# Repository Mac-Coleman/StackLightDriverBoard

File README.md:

# Stack Light Driver Board

This repository hosts my KiCad project.

Currently there is only a schematic.

Footprints and 3D models of most components are provided by [CDFER's JLCPCB component library for KiCad](https://github.com/CDFER/JLCPCB-Kicad-Library).

## Footprints and 3D models of the following components provided by SnapMagic:
* TSR_1-2433E
* 282837-2
* B2B-XH-A
* ESP32-S3-WROOM-1-N4
* PJ-102AH

## 3D models provided by Adafruit:
* MAX98357

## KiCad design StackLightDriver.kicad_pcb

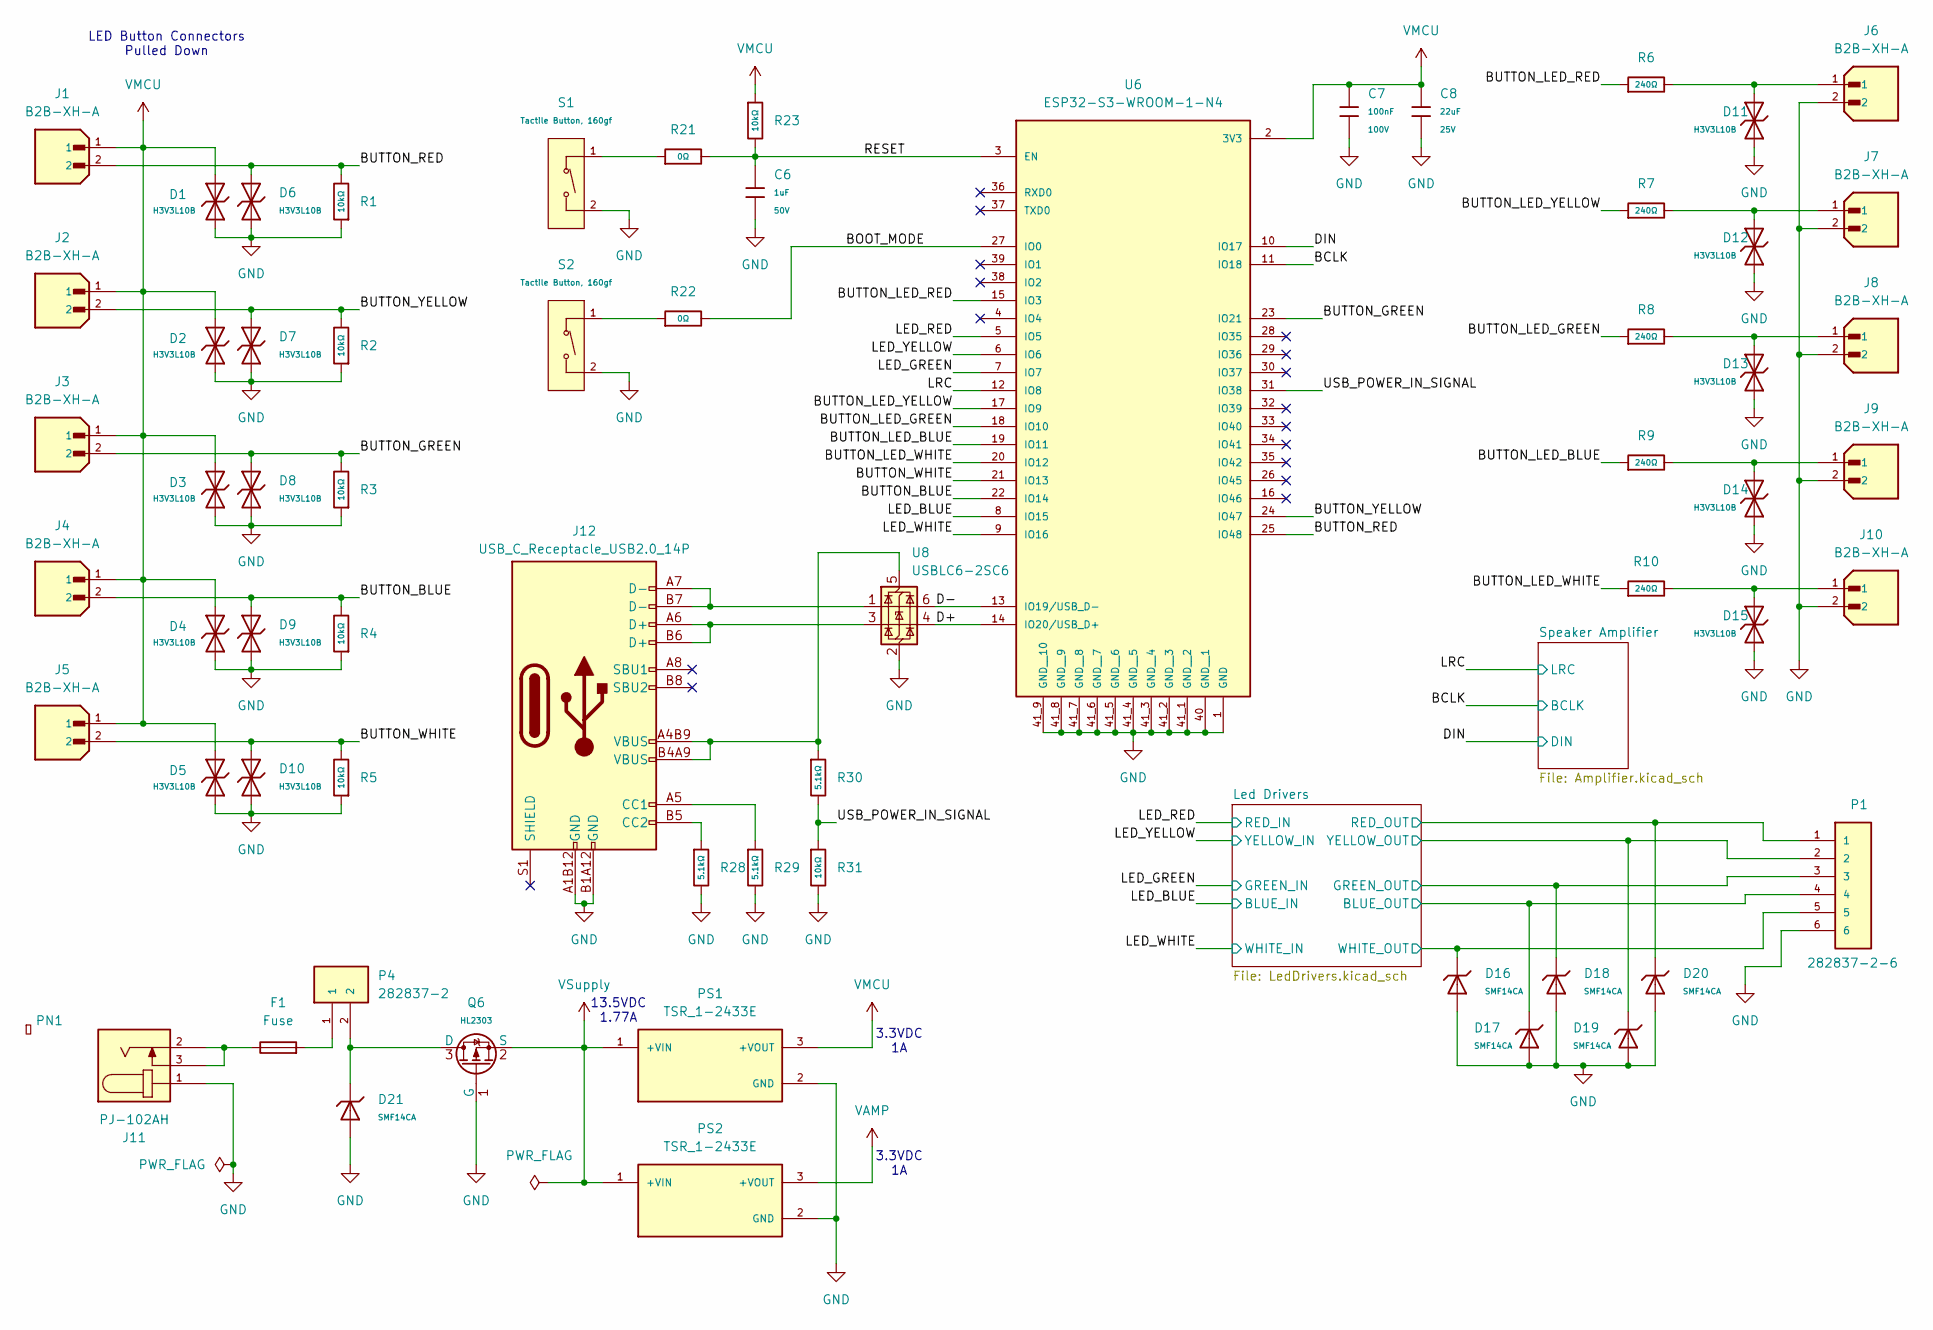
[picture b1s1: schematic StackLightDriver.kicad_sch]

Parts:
C6: 1uF; C_0805; Voltage Rated 50V; Tolerance ±10%; Part CL21B105KBFNNNE; LCSC C28323
C7: 100nF; C_0805; Voltage Rated 100V; Tolerance ±10%; Part CL21B104KCFNNNE; LCSC C28233
C8: 22uF; C_0805; Voltage Rated 25V; Tolerance ±20%; Part CL21A226MAQNNNE; LCSC C45783
D1, D2, D3, D4, D5, D6, D7, D8, D9, D10, D11, D12, D13, D14, D15: H3V3L10B; D_DFN1006-2L; Breakdown Voltage 5.5V; Part H3V3L10B; LCSC C20615781
D16, D17, D18, D19, D20, D21: SMF14CA; D_SOD-123FL; Part SMF14CA; LCSC C41411783
F1: Fuse; Fuseholder_Clip-5x20mm_Littelfuse_111_Lateral_P18.80x5.00mm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
J1, J2, J3, J4, J5, J6, J7, J8, J9, J10: B2B-XH-A; JST_B2B-XH-A; PARTREV N/A
J11: PJ-102AH; CUI_PJ-102AH
J12: USB_C_Receptacle_USB2.0_14P
P1: 282837-2-6; TE_282837-2-6; PARTREV G3
P4: 282837-2; TE_282837-2; PARTREV G3
PN1: Part_Num_JLCPCB
PS1, PS2: TSR_1-2433E; CONV_TSR_1-2433E; PARTREV May 25, 2020
Q6: HL2303; Q_SOT-23; Part HL2303; LCSC C7420345
R1, R2, R3, R4, R5, R23, R31: 10kΩ; R_0805; Overload Voltage (Max) 150V; Tolerance ±1%; Part 0805W8F1002T5E; LCSC C17414
R6, R7, R8, R9, R10: 240Ω; R_0805; Overload Voltage (Max) 150V; Tolerance ±1%; Part 0805W8F2400T5E; LCSC C17572
R21, R22: 0Ω; R_0805; Overload Voltage (Max) 150V; Tolerance ±1%; Part 0805W8F0000T5E; LCSC C17477
R28, R29, R30: 5.1kΩ; R_0805; Overload Voltage (Max) 150V; Tolerance ±1%; Part 0805W8F5101T5E; LCSC C27834
S1, S2: Tactile Button, 160gf; SW_TS-1088-AR02016; Voltage Rating (Dc) 12V; Part TS-1088-AR02016; LCSC C720477
U6: ESP32-S3-WROOM-1-N4; XCVR_ESP32-S3-WROOM-1-N4; PARTREV v1.0; Digikey 1965-ESP32-S3-WROOM-1-N4CT-ND
U8: USBLC6-2SC6; SOT-23-6; Digikey 497-5235-1-ND

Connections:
/BCLK: U6.11 (IO18); also elsewhere on the board
/BOOT_MODE: R22.2, U6.27 (IO0)
/BUTTON_BLUE: D9.2, J4.2, R4.2, U6.22 (IO14)
/BUTTON_GREEN: D8.2, J3.2, R3.2, U6.23 (IO21)
/BUTTON_LED_BLUE: R9.1, U6.19 (IO11)
/BUTTON_LED_GREEN: R8.1, U6.18 (IO10)
/BUTTON_LED_RED: R6.1, U6.15 (IO3)
/BUTTON_LED_WHITE: R10.1, U6.20 (IO12)
/BUTTON_LED_YELLOW: R7.1, U6.17 (IO9)
/BUTTON_RED: D6.2, J1.2, R1.2, U6.25 (IO48)
/BUTTON_WHITE: D10.2, J5.2, R5.2, U6.21 (IO13)
/BUTTON_YELLOW: D7.2, J2.2, R2.2, U6.24 (IO47)
/D+: U6.14 (IO20/USB_D+), U8.4 (I/O2)
/D-: U6.13 (IO19/USB_D-), U8.6 (I/O1)
/DIN: U6.10 (IO17); also elsewhere on the board
/LED_BLUE: U6.8 (IO15); also elsewhere on the board
/LED_GREEN: U6.7 (IO7); also elsewhere on the board
/LED_RED: U6.5 (IO5); also elsewhere on the board
/LED_WHITE: U6.9 (IO16); also elsewhere on the board
/LED_YELLOW: U6.6 (IO6); also elsewhere on the board
/LRC: U6.12 (IO8); also elsewhere on the board
/Led Drivers/BLUE_OUT: D17.1, P1.4; also elsewhere on the board
/Led Drivers/GREEN_OUT: D18.1, P1.3; also elsewhere on the board
/Led Drivers/RED_OUT: D20.1, P1.1; also elsewhere on the board
/Led Drivers/WHITE_OUT: D16.1, P1.5; also elsewhere on the board
/Led Drivers/YELLOW_OUT: D19.1, P1.2; also elsewhere on the board
/RESET: C6.1, R21.2, R23.2, U6.3 (EN)
/USB_POWER_IN_SIGNAL: R30.2, R31.1, U6.31 (IO38)
GND: C6.2, C7.2, C8.2, D1.1, D2.1, D3.1, D4.1, D5.1, D6.1, D7.1, D8.1, D9.1, D10.1, D11.1, D12.1, D13.1, D14.1, D15.1, D16.2, D17.2, D18.2, D19.2, D20.2, D21.2, J6.2, J7.2, J8.2, J9.2, J10.2, J11.1, J12.A1B12 (GND), J12.B1A12 (GND), P1.6, PS1.2 (GND), PS2.2 (GND), Q6.1 (G), R1.1, R2.1, R3.1, R4.1, R5.1, R28.2, R29.2, R31.2, S1.2 (B), S2.2 (B), U6.1 (GND), U6.40 (GND__1), U6.41_1 (GND__2), U6.41_2 (GND__3), U6.41_3 (GND__4), U6.41_4 (GND__5), U6.41_5 (GND__6), U6.41_6 (GND__7), U6.41_7 (GND__8), U6.41_8 (GND__9), U6.41_9 (GND__10), U6.41_10 (GND__11), U6.41_11 (GND__12), U6.41_12 (GND__13), U6.41_13 (GND__14), U6.41_14 (GND__15), U6.41_15 (GND__16), U6.41_16 (GND__17), U6.41_17 (GND__18), U6.41_18 (GND__19), U6.41_19 (GND__20), U6.41_20 (GND__21), U6.41_21 (GND__22), U8.2 (GND); also elsewhere on the board
unnamed: D11.2, J6.1, R6.2
unnamed: D12.2, J7.1, R7.2
unnamed: D13.2, J8.1, R8.2
unnamed: D14.2, J9.1, R9.2
unnamed: D15.2, J10.1, R10.2
unnamed: F1.1, J11.2, J11.3
unnamed: F1.2, P4.1
unnamed: J12.A5 (CC1), R29.1
unnamed: J12.B5 (CC2), R28.1
unnamed: J12.A6 (D+), J12.B6 (D+), U8.3 (I/O2)
unnamed: J12.A7 (D-), J12.B7 (D-), U8.1 (I/O1)
unnamed: D21.1, P4.2, Q6.3 (D)
unnamed: R21.1, S1.1 (A)
unnamed: R22.1, S2.1 (A)
unnamed: J12.A4B9 (VBUS), J12.B4A9 (VBUS), R30.1, U8.5 (VBUS)
VAMP: PS2.3 (+VOUT); also elsewhere on the board
VMCU: C7.1, C8.1, D1.2, D2.2, D3.2, D4.2, D5.2, J1.1, J2.1, J3.1, J4.1, J5.1, PS1.3 (+VOUT), R23.1, U6.2 (3V3)
VSupply: PS1.1 (+VIN), PS2.1 (+VIN), Q6.2 (S); also elsewhere on the board

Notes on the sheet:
3.3VDC 1A
13.5VDC 1.77A
LED Button Connectors Pulled Down

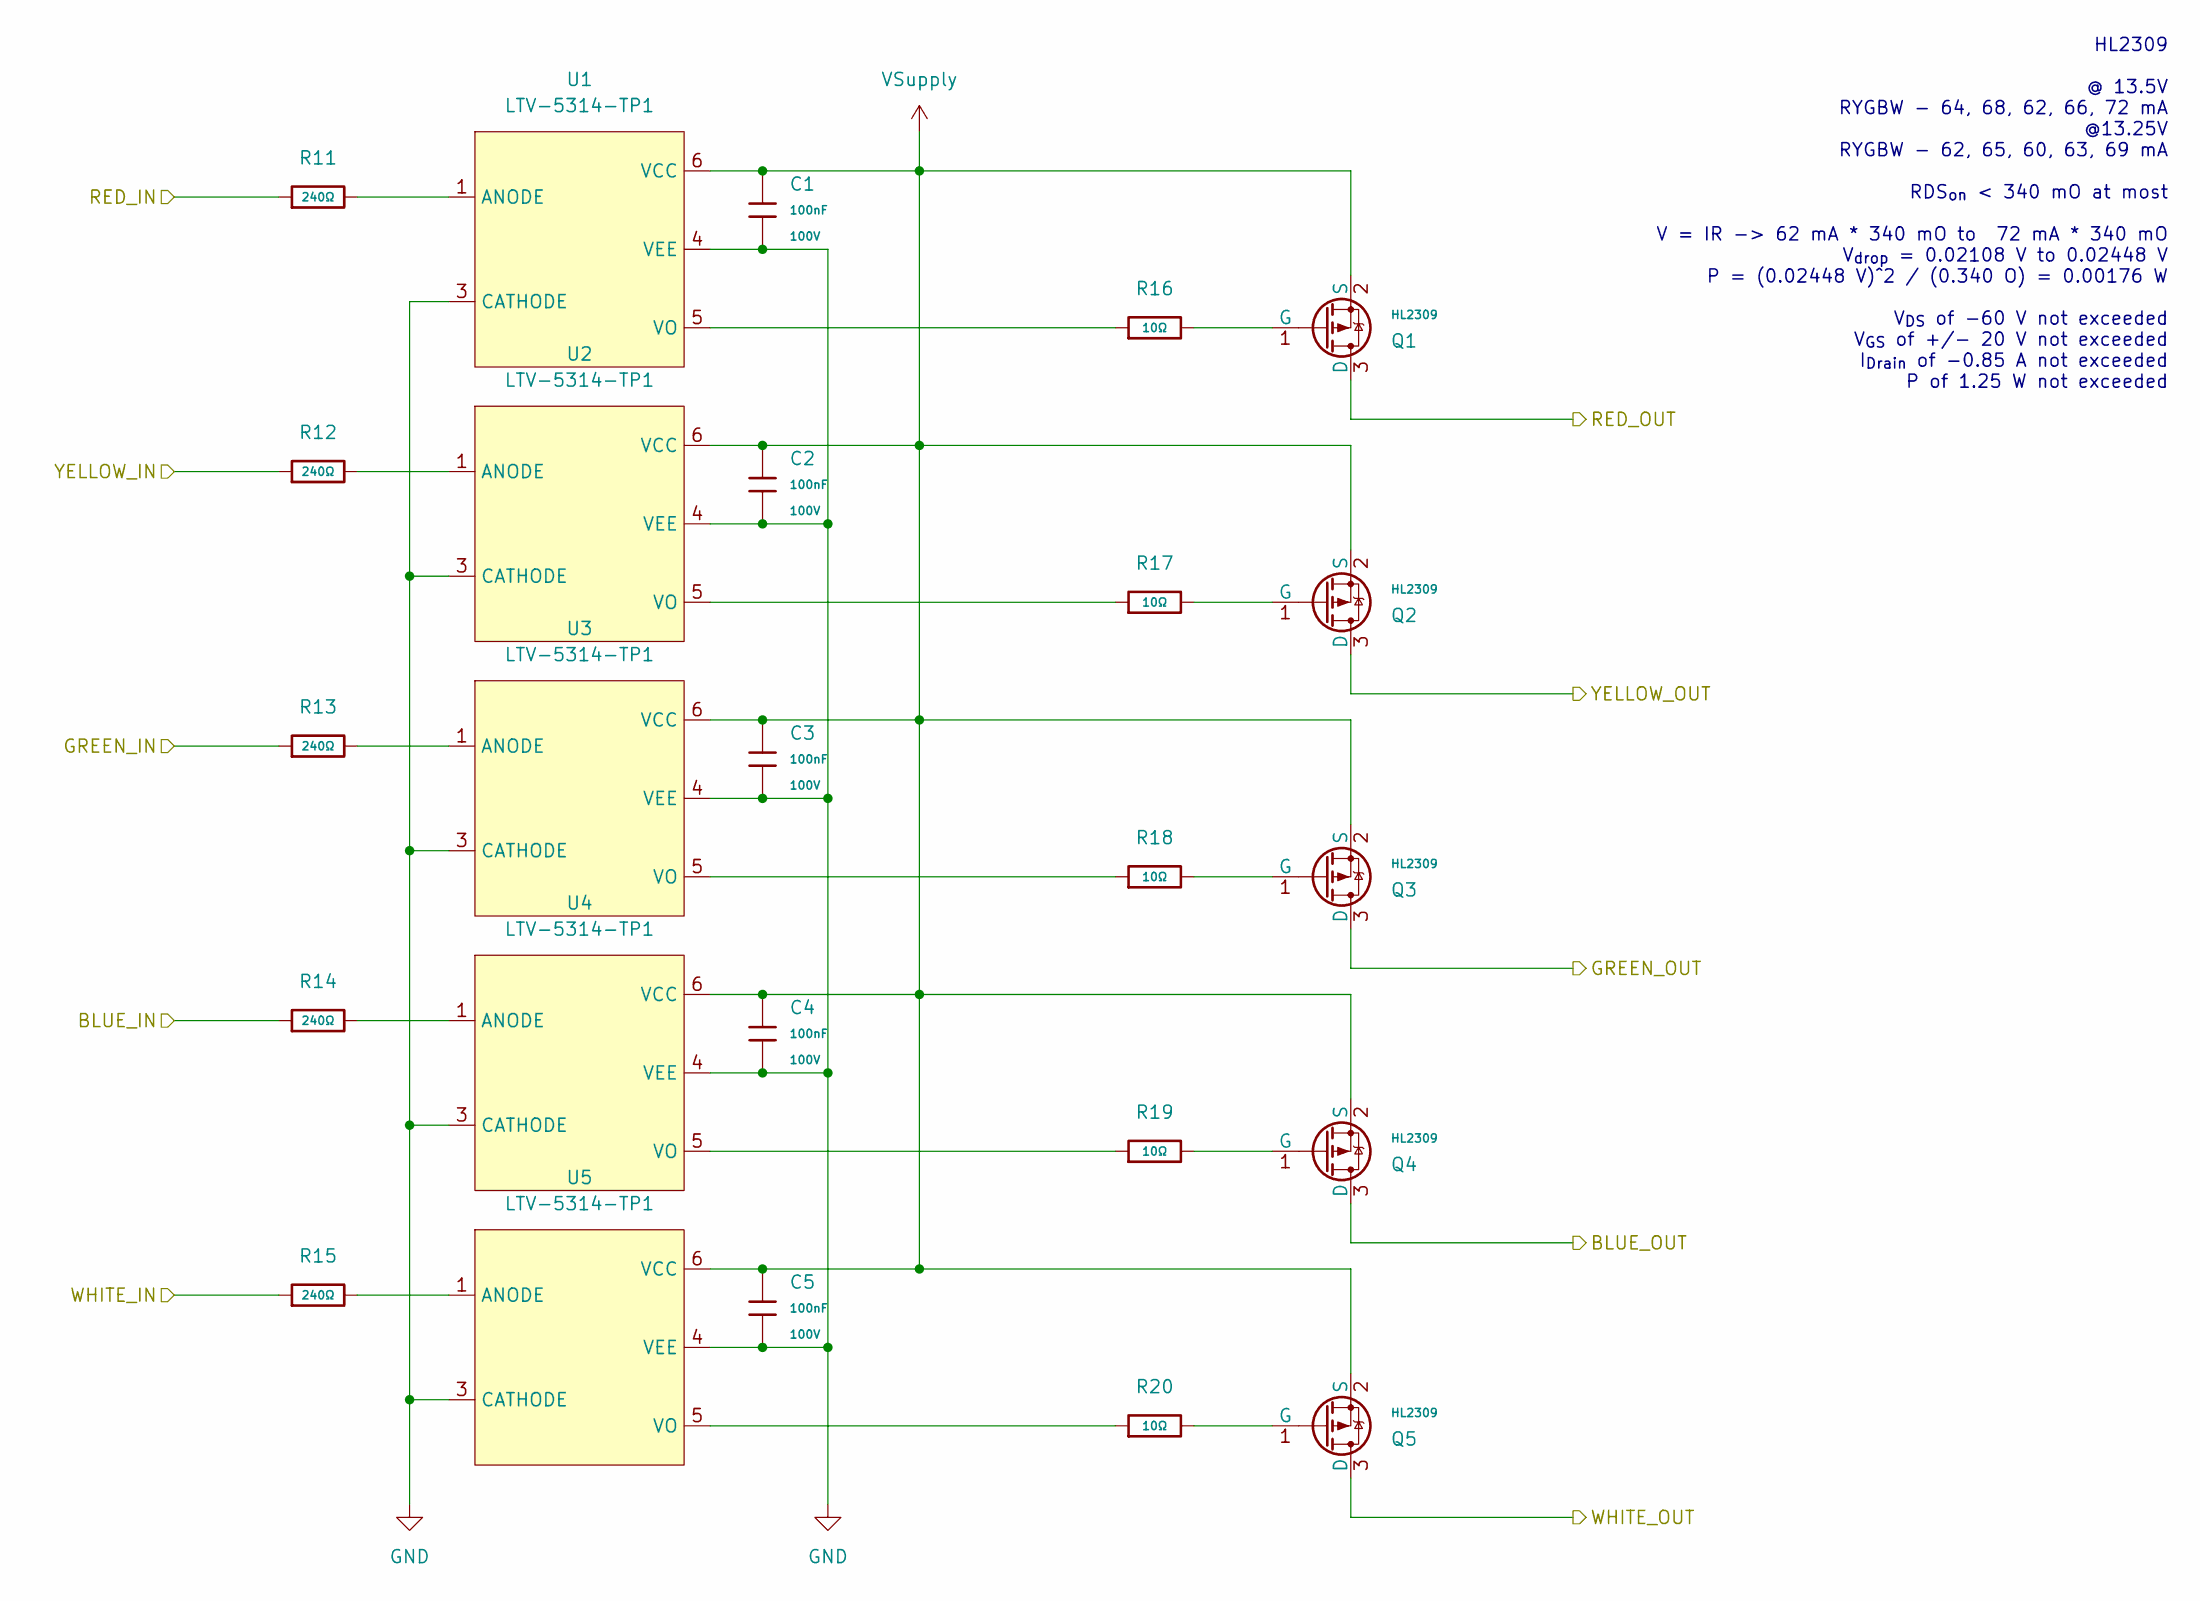
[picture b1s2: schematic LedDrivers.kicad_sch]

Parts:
C1, C2, C3, C4, C5: 100nF; C_0805; Voltage Rated 100V; Tolerance ±10%; Part CL21B104KCFNNNE; LCSC C28233
Q1, Q2, Q3, Q4, Q5: HL2309; Q_SOT-23; Part HL2309; LCSC C28646263
R11, R12, R13, R14, R15: 240Ω; R_0805; Overload Voltage (Max) 150V; Tolerance ±1%; Part 0805W8F2400T5E; LCSC C17572
R16, R17, R18, R19, R20: 10Ω; R_0805; Overload Voltage (Max) 150V; Tolerance ±1%; Part 0805W8F100JT5E; LCSC C17415
U1, U2, U3, U4, U5: LTV-5314-TP1; LCSC C2944034

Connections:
/LED_BLUE: R14.1; also elsewhere on the board
/LED_GREEN: R13.1; also elsewhere on the board
/LED_RED: R11.1; also elsewhere on the board
/LED_WHITE: R15.1; also elsewhere on the board
/LED_YELLOW: R12.1; also elsewhere on the board
/Led Drivers/BLUE_OUT: Q4.3 (D); also elsewhere on the board
/Led Drivers/GREEN_OUT: Q3.3 (D); also elsewhere on the board
/Led Drivers/RED_OUT: Q1.3 (D); also elsewhere on the board
/Led Drivers/WHITE_OUT: Q5.3 (D); also elsewhere on the board
/Led Drivers/YELLOW_OUT: Q2.3 (D); also elsewhere on the board
GND: C1.2, C2.2, C3.2, C4.2, C5.2, U1.3 (CATHODE), U1.4 (VEE), U2.3 (CATHODE), U2.4 (VEE), U3.3 (CATHODE), U3.4 (VEE), U4.3 (CATHODE), U4.4 (VEE), U5.3 (CATHODE), U5.4 (VEE); also elsewhere on the board
unnamed: Q1.1 (G), R16.2
unnamed: Q2.1 (G), R17.2
unnamed: Q3.1 (G), R18.2
unnamed: Q4.1 (G), R19.2
unnamed: Q5.1 (G), R20.2
unnamed: R11.2, U1.1 (ANODE)
unnamed: R16.1, U1.5 (VO)
unnamed: R12.2, U2.1 (ANODE)
unnamed: R17.1, U2.5 (VO)
unnamed: R13.2, U3.1 (ANODE)
unnamed: R18.1, U3.5 (VO)
unnamed: R14.2, U4.1 (ANODE)
unnamed: R19.1, U4.5 (VO)
unnamed: R15.2, U5.1 (ANODE)
unnamed: R20.1, U5.5 (VO)
VSupply: C1.1, C2.1, C3.1, C4.1, C5.1, Q1.2 (S), Q2.2 (S), Q3.2 (S), Q4.2 (S), Q5.2 (S), U1.6 (VCC), U2.6 (VCC), U3.6 (VCC), U4.6 (VCC), U5.6 (VCC); also elsewhere on the board

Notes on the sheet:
HL2309 @ 13.5V RYGBW - 64, 68, 62, 66, 72 mA @13.25V RYGBW - 62, 65, 60, 63, 69 mA RDS_{on} < 340 mO at most V = IR -> 62 mA * 340 mO to 72 mA * 340 mO V_{drop} = 0.02108 V to 0.02448 V P = (0.02448 V)^2 / (0.340 O) = 0.00176 W V_{DS} of -60 V not exceeded V_{GS} of +/- 20 V not exceeded I_{Drain} 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

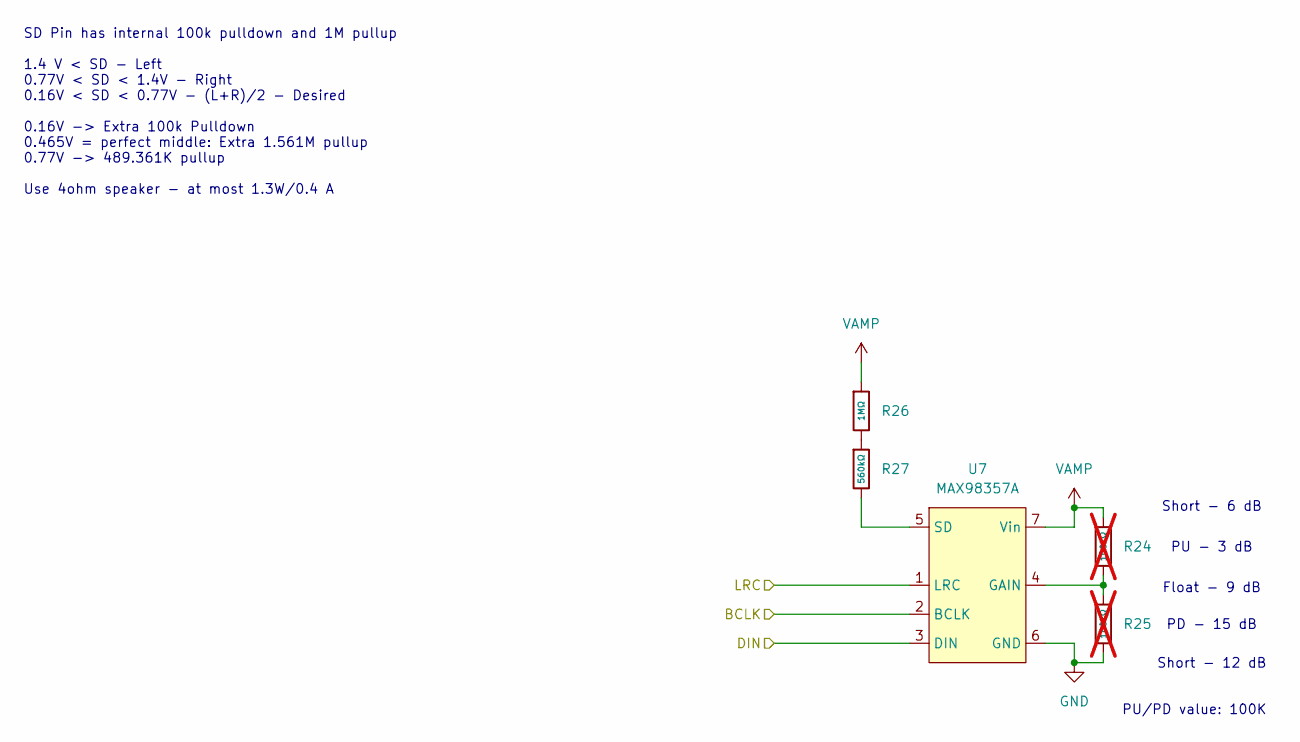
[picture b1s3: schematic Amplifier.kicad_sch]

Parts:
R24, R25: 100kΩ; R_0805; Overload Voltage (Max) 150V; Tolerance ±1%; Part 0805W8F1003T5E; LCSC C149504; not fitted
R26: 1MΩ; R_0805; Overload Voltage (Max) 150V; Tolerance ±1%; Part 0805W8F1004T5E; LCSC C17514
R27: 560kΩ; R_0603; Overload Voltage (Max) 75V; Tolerance ±1%; Part 0603WAF5603T5E; LCSC C23203
U7: MAX98357A; Adafruit_I2S_MAX98357A

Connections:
/BCLK: U7.2 (BCLK); also elsewhere on the board
/DIN: U7.3 (DIN); also elsewhere on the board
/LRC: U7.1 (LRC); also elsewhere on the board
GND: R25.2, U7.6 (GND); also elsewhere on the board
unnamed: R26.2, R27.1
unnamed: R24.2, R25.1, U7.4 (GAIN)
unnamed: R27.2, U7.5 (SD)
VAMP: R24.1, R26.1, U7.7 (Vin); also elsewhere on the board

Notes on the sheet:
PD - 15 dB
PU - 3 dB
Short - 6 dB
Float - 9 dB
SD Pin has internal 100k pulldown and 1M pullup 1.4 V < SD - Left 0.77V < SD < 1.4V - Right 0.16V < SD < 0.77V - (L+R)/2 - Desired 0.16V -> Extra 100k Pulldown 0.465V = perfect middle: Extra 1.561M pullup 0.77V -> 489.361K pullup Use 4ohm speaker - at most 1.3W/0.4 A
PU/PD value: 100K
Short - 12 dB

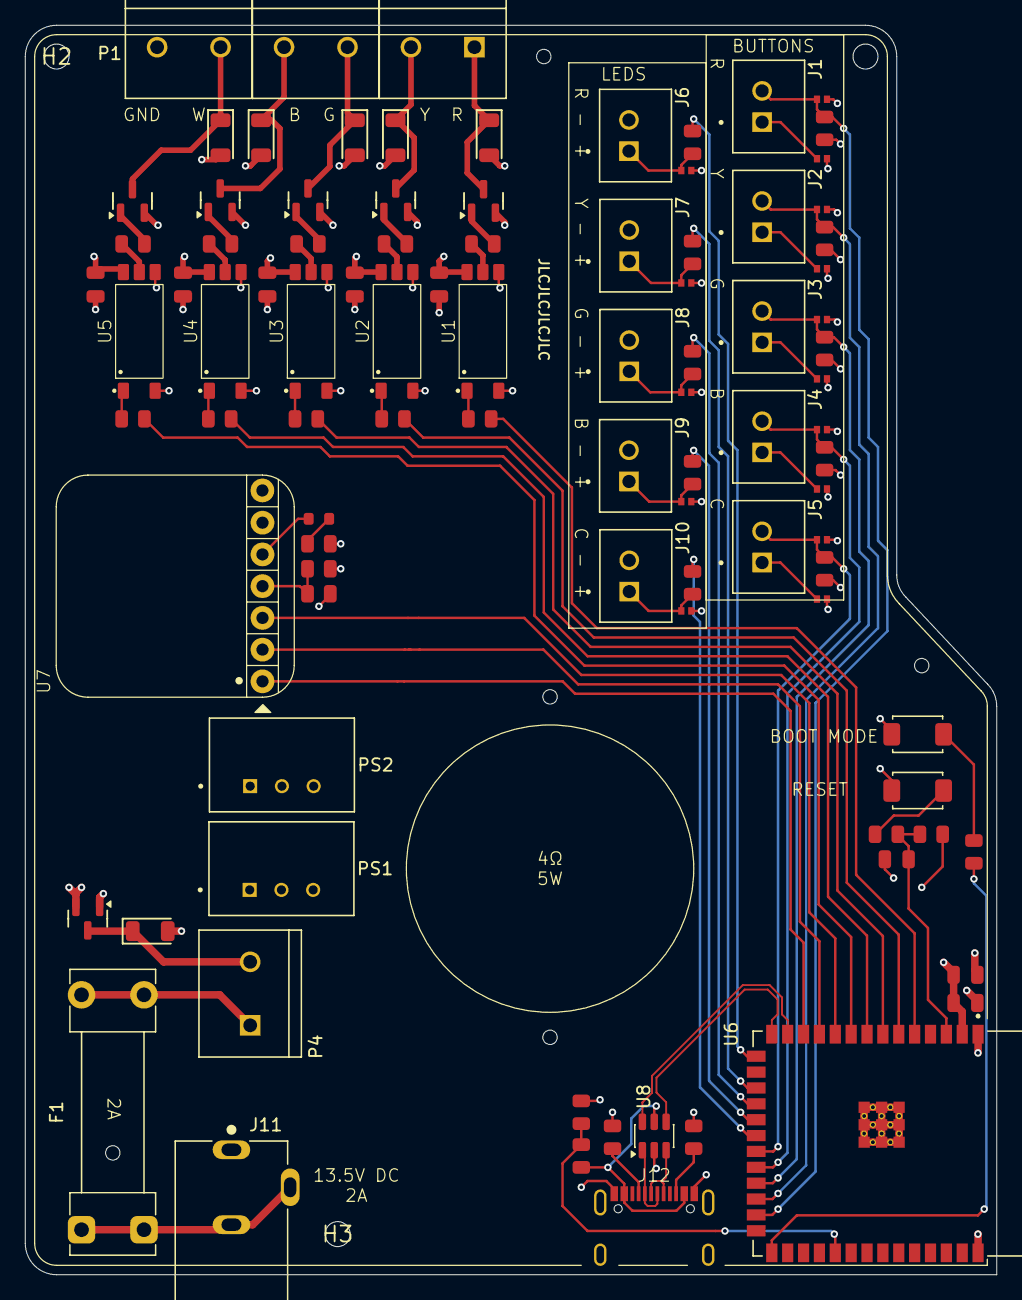
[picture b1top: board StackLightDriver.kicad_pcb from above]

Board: 4 copper layers, 77.8 x 100.0 mm, 102 parts (0 on the bottom side), 65 nets.

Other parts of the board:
H1: Mounting_hole
H2: Mounting Hole
H3: Mounting hole
H4, H5, H6, H7, H8: Tooling_hole

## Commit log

2025-12-15 Added README
2025-12-16 Recreated symbol/footprint libraries, added 3D models and Git LFS
2025-12-16 Updated .gitignore
2025-12-16 Attribution of 3D models/symbols/footprints from SnapMagic
2025-12-16 Copied PCM_JLCPCB tactile switch symbol to change pins to passive for ERC
2025-12-16 Added 3D model and footprint for power jack
2025-12-16 Rearranged ESP32 symbol, added note file
2025-12-17 Added USB C connections and USB C TVS diodes
2026-01-19 Added basic Littelfuse clip model, began laying out PCB
    Still needs revisions to TVS diodes.
2026-01-20 Added fuse models, LTV5314 models (Just step files for now)
2026-01-20 Rearranged components slightly, situating ESP32 better
2026-01-21 Added models and footprint for Adafruit Max98357
2026-01-22 Added some TVS diodes to schematic and to PCB layout
2026-01-26 Removed Test Points, reordered fuse and switch
2026-01-26 Updated USB C connector schematic symbol and added voltage divider
2026-02-04 Added reverse polarity mosfet
2026-02-04 Added footprint for USB-C receptacle
2026-02-04 Fixed incorrect decoupling capacitance on LTV5314
2026-02-04 Placed TVS diodes on board
2026-02-09 First routing attempt
2026-02-09 DRC adjustments
2026-02-10 Mounting and tooling holes, silkscreen work
2026-02-11 Changed terminal block footprint, silkscreen changes, holes for speaker
2026-02-11 Silly silk screen stuff, re-verified ESP32 pins
2026-02-12 Terminal block courtyard, mounting/tooling hole references
